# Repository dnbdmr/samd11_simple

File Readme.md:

Simple breakout board for a soic-16 SAMD11C14A
- Micro USB
- all other pins broken out
- .5" wide. not too much space on breadboard.

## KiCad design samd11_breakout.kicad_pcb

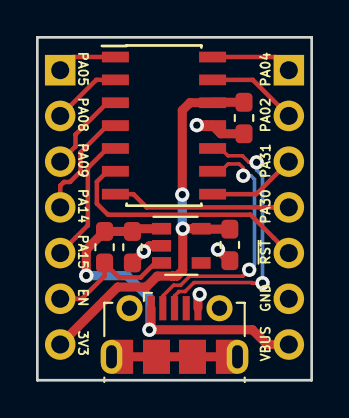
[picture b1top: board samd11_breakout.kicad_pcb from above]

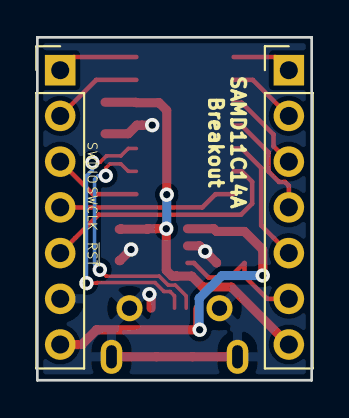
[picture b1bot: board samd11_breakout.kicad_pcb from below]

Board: 2 copper layers, 15.2 x 19.1 mm, 9 parts (2 on the bottom side), 15 nets.

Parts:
C1, C2: 10uF; C_0603_1608Metric_Pad1.05x0.95mm_HandSolder
C3: 100nF; C_0603_1608Metric_Pad1.05x0.95mm_HandSolder
J1, J2: Conn_01x07_Male; PinHeader_1x07_P2.54mm_Vertical
J3: USB_B_Micro; USB_Micro-B_Molex-105017-0001
R1: 100k; R_0603_1608Metric_Pad1.05x0.95mm_HandSolder
U1: AP2127K-3.3; SOT-23-5
U2: ATSAMD11C14A-SS; SOIC-14_3.9x8.7mm_P1.27mm

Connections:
+3V3: C2.1, C3.1, J1.7, U1.5, U2.12
/D+: J3.3, U2.10
/D-: J3.2, U2.9
/EN: J1.6, R1.2, U1.3
/PA02: J2.2, U2.13
/PA04: J2.1, U2.14
/PA05: J1.1, U2.1
/PA08: J1.2, U2.2
/PA09: J1.3, U2.3
/PA14: J1.4, U2.4
/PA15: J1.5, U2.5
/PA30: J2.4, U2.7
/PA31: J2.3, U2.8
GND: C1.2, C2.2, C3.2, J2.6, J3.5, J3.6, U1.2, U2.11
VBUS: C1.1, J2.7, J3.1, R1.1, U1.1

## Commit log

2019-10-31 Initial commit. Rev A complete and archived.
2019-11-25 Added todo, silkscreen font size
2020-06-18 Added pinout spreadsheet
2020-06-18 Create LICENSE
2020-11-12 Add readme, pdf.
2020-11-13 Fix Readme
